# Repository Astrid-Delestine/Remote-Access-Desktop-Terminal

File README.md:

R-DAT 

# NOW IN BETA!

### Notes:

* This project has graduated from a coursework project to a personal project of mine (Astrid)
* Any text with a line thru it will be removed in the next revision (if I remember)
* A **MAJOR** rebuild was done for this version, and as such I do not belive everyting will work out of the gate. 
* Refer to the dev branch for the most up to date snapshots
* Refer to the Alpha branch for the final alpha version
* Refer to the Beta branch for the current Beta version

~~The R-DAT will use a Latte pana MU 8gb [here](https://www.lattepanda.com/lattepanda-mu) & sold [here](https://www.dfrobot.com/kit-004.html?tracking=LATTEPANDAMU) with their github linked [here](https://github.com/LattePandaTeam/LattePanda-Mu).
It can operate at anywhere from 9-20v.~~

~~All project requirements are listed in [here](./Legacy/CourseDocs/proj_req.md)~~

~~For the midterm review please look [here](./Legacy/CourseDocs/MidtermReview.md)~~

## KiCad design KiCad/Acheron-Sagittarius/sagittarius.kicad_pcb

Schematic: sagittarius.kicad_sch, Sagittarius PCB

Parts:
C1: 4.7u; C_0603_1608Metric
C2, C3, C4, C7: 100n; C_0603_1608Metric
C5: 10u; C_0603_1608Metric
C6: 10n; C_0603_1608Metric
C8, C9: 1u; C_0805_2012Metric_Pad1.15x1.40mm_HandSolder
C10, C11: 10n; C_0805_2012Metric_Pad1.15x1.40mm_HandSolder
C12, C13, C14, C15, C16, C17, C18, C19, C20, C21: 100n; C_0805_2012Metric_Pad1.15x1.40mm_HandSolder
CB1: 100n; C_0805_2012Metric_Pad1.15x1.40mm_HandSolder
D1, D2, D3, D4, D5, D6, D7, D8, D9, D10, D11, D12, D13, D14, D15, D16, D17, D18, D19, D20, D21, D22, D23, D24, D25, D26, D27, D28, D29, D30, D31, D32, D33, D34, D35, D36, D37, D38, D39, D40, D41, D42, D43, D44, D45, D46, D47, D48, D49, D50, D51, D52, D53, D54, D55, D56, D57, D58, D59, D60, D61, D62, D63, D64, D65, D66, D67, D68, D69, D70, D71, D72, D74, D75, D76, D77: 1N4148; D_SOD-123
D73: RB060M-60TR; D_SOD-123; Manufacturer Part No RB060M-60TR; LCSC Part No C114257
D78, D79, D80, D81, D82, D83, D84, D85: WS2812-2020; LED_WS2812_2020; Manufacturer Part No WS2812-2020
FB1: 150R@100MHz; L_1812_4532Metric_Pad1.30x3.40mm_HandSolder; Manufacturer Part No FCM3216KF-151T09; LCSC Part No C155090
G1: Lambda; lambda
G2: Cannon Keys Logo; cannon_logo_11.5x7.9mm
G3: Gamma2; gamma2
G4: Acheron Logo; acheronShort_0.3x0.5in_Plated
G5: Delta; delta
G6: Sagittarius Logo; sagittariusLogo_21.4x15.6
G7: Epsilon; epsilon
G8: Sigma; sigma
G9: Sagittarius Name; sagittariusName
G10: Tau; tau
G11: Sagittarius Poem; sagittariusPoem
G12: Phi; phi
G13: Sagittarius Label; sagittariusLabel_30x11.7mm
G14: Zeta; zeta
GR1: Right Space Warning Sign; warning_sign_3.6x3.2mm
GR2: ISO Backslash Warning Sign; warning_sign_3.6x3.2mm
GR3: Split Left Shift Warning Sign; warning_sign_3.6x3.2mm
GR4: Backspace Warning Sign; warning_sign_3.6x3.2mm
J1: Conn_ARM_JTAG_SWD_10
J2: SM04B-SRSS; JST_SM04B-SRSS; Manufacturer Part No SM04B-SRSS-TB(LF)(SN); LCSC Part No C160404
LED1, LED2, LED3, LED4, LED5, LED6, LED7, LED8, LED9, LED10, LED11, LED12, LED13, LED14, LED15, LED16, LED17, LED18, LED19, LED20, LED21, LED22, LED23, LED24, LED25, LED26, LED27, LED28, LED29, LED30, LED31, LED32, LED33, LED34, LED35, LED36, LED37, LED38, LED39, LED40, LED41, LED42, LED43, LED44, LED45, LED46, LED47, LED48, LED49, LED50, LED51, LED52, LED53, LED54, LED55, LED56, LED57, LED58, LED59, LED60, LED61, LED62, LED63, LED64, LED65, LED66, LED67, LED68, LED69, LED70, LED71, LED72, LED73, LED74, LED75, LED76, LED77, LED78, LED79, LED80, LED81, LED82, LED83, LED84: LED; LED_THT_2.54mm
Q1: AO3401A; SOT-23; Manufacturer Part No AO3401; LCSC Part No C427383
Q2: DTC123JKAT146; SOT-23; Manufacturer Part No DTC123JKAT146; LCSC Part No C111724
R1, R5, R6, R7, R8, R17, R18: 10k; R_0805_2012Metric_Pad1.15x1.40mm_HandSolder
R2, R3: 100k; R_0805_2012Metric_Pad1.15x1.40mm_HandSolder
R4, R19: 100R; R_0805_2012Metric_Pad1.15x1.40mm_HandSolder
R9, R10, R11, R12, R13, R14, R15, R16: 3R; R_0805_2012Metric_Pad1.15x1.40mm_HandSolder
RL1, RL2, RL3, RL4, RL5, RL6, RL7, RL8, RL9, RL10, RL11, RL12, RL13, RL14, RL15, RL16, RL17, RL18, RL19, RL20, RL21, RL22, RL23, RL24, RL25, RL26, RL27, RL28, RL29, RL30, RL31, RL32, RL33, RL34, RL35, RL36, RL37, RL38, RL39, RL40, RL41, RL42, RL43, RL44, RL45, RL46, RL47, RL48, RL49, RL50, RL51, RL52, RL53, RL54, RL55, RL56, RL57, RL58, RL59, RL60, RL61, RL62, RL63, RL64, RL65, RL66, RL67, RL68, RL69, RL70, RL71, RL72, RL73, RL74, RL75, RL76, RL77: 420; R_0805_2012Metric_Pad1.15x1.40mm_HandSolder
ROT1, ROT2, ROT3, ROT4: EC11Ex; ALPS_EC11E
S1: PCM12SMTR; SW_SPDT_PCM12; Manufacturer Part No PCM12SMTR; LCSC Part No C221841
S2: SKQGADE010; K2-1187SQ-A4SW-06; Manufacturer Part No SKQGADE010; LCSC Part No C116647
SW1: PGUP; MX100
SW2: ESC; MX100
SW3: 1; MX100
SW4: 2; MX100
SW5: 3; MX100
SW6: 4; MX100
SW7: 5; MX100
SW8: 6; MX100
SW9: 7; MX100
SW10: 8; MX100
SW11: 9; MX100
SW12: 10; MX100
SW13: MINUS; MX100
SW14: PLUS; MX100
SW15: LEFT_BACKSPACE; MX100
SW16: RIGHT BACKSPACE; MX100
SW17: 2U BACKSPACE; MX200
SW18: PGDN; MX100
SW19: TAB; MX150
SW20: Q; MX100
SW21: W; MX100
SW22: E; MX100
SW23: R; MX100
SW24: T; MX100
SW25: Y; MX100
SW26: U; MX100
SW27: I; MX100
SW28: O; MX100
SW29: P; MX100
SW30: LBRACE; MX100
SW31: RBRACE; MX100
SW32: BKSLSH; MX150
SW33: HOME; MX100
SW34: CAPS LOCK; MX175
SW35: A; MX100
SW36: S; MX100
SW37: D; MX100
SW38: F; MX100
SW39: G; MX100
SW40: H; MX100
SW41: J; MX100
SW42: K; MX100
SW43: L; MX100
SW44: COLON; MX100
SW45: QUOTE; MX100
SW46: ISO_TILDE; MX100
SW47: ANSI_ENTER; MX225
SW48: ISO_ENTER; MX_ISOEnter_Vertical_LED
SW49: STEPPED CAPS; MX125
SW50: END; MX100
SW51: 225_LSHIFT; MX225
SW52: ISO_BLACKSLASH; MX100
SW53: Z; MX100
SW54: X; MX100
SW55: C; MX100
SW56: V; MX100
SW57: B; MX100
SW58: N; MX100
SW59: M; MX100
SW60: COMMA; MX100
SW61: DOT; MX100
SW62: SLASH; MX100
SW63: 225_RSHIFT; MX225
SW64: UP; MX100
SW65: SPLIT_RSHIFT_FN; MX100
SW66: 125_LSHIFT; MX125
SW67: 125_RSHIFT; MX125
SW68: LCTRL; MX150
SW69: LGUI; MX125
SW70: 1U_LSPACE; MX100
SW71: 225_LSPACE; MX225
SW72: 275_RSPACE; MX275
SW73: 100_RSPACE; MX100
SW74: DOWN; MX100
SW75: RIGHT; MX100
SW76: 175_LSPACE; MX175
SW77: 150_LSPACE; MX150
SW78: 150_RALT; MX150
SW79: 150_RCTRL; MX150
SW80: 175_RSPACE; MX175
SW81: LEFT; MX100
U1: STM32F072-LQFP48; LQFP-48_7x7mm_P0.5mm; Manufacturer Part No STM32F072CBT6; LCSC Part No C81720
U2: MCP1700-3302E_SOT23; SOT-23; Manufacturer Part No MCP1700-3302E/TT; LCSC Part No C39051
U3: TXS0101; SOT-23-6; Manufacturer Part Number TXS0101DBVR; LCSC Part Number C132604

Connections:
3V3: C1.2, C2.2, C3.2, C4.2, C5.1, C6.1, C7.2, C9.2, C12.2, D73.2 (A), J1.1 (VTref), R3.1, R5.2, R6.2, R17.1, S1.3 (C), U1.1 (VBAT), U1.9 (VDDA), U1.24 (VDD), U1.36 (VDDIO2), U1.48 (VDD), U2.2 (VO), U3.1 (VCCA), U3.5 (OE)
5V: C8.2, C13.1, D73.1 (K), J2.1, Q1.2 (S), R2.1, R9.1, R10.1, R11.1, R12.1, R13.1, R14.1, R15.1, R16.1, R18.2, U2.3 (VI), U3.6 (VCCB)
BOOT0: R1.2, U1.44 (BOOT0)
Col1: ROT1.S1, ROT2.S1, ROT3.S1, ROT4.S1, SW1.1 (Col), SW18.1 (Col), SW33.1 (Col), SW50.1 (Col), SW68.1 (Col), U1.17 (PA7/TIM3_CH2/TIM14_CH1/ADC_IN7)
Col2: SW2.1 (Col), SW19.1 (Col), SW34.1 (Col), SW49.2 (Row), SW51.1 (Col), SW66.1 (Col), SW69.1 (Col), U1.15 (PA5/ADC_IN5/DAC_OUT2)
Col3: SW3.1 (Col), SW20.1 (Col), SW35.1 (Col), SW52.1 (Col), U1.14 (PA4/TIM14_CH1/ADC_IN4)
Col4: SW4.1 (Col), SW21.1 (Col), SW36.1 (Col), SW53.1 (Col), U1.13 (PA3/TIM15_CH2/ADC_IN3)
Col5: SW5.1 (Col), SW22.1 (Col), SW37.1 (Col), SW54.1 (Col), U1.12 (PA2/ADC_IN2)
Col6: SW6.1 (Col), SW23.1 (Col), SW38.1 (Col), SW55.1 (Col), U1.11 (PA1/ADC_IN1)
Col7: SW7.1 (Col), SW24.1 (Col), SW39.1 (Col), SW56.1 (Col), SW70.1 (Col), SW76.2 (Row), U1.10 (PA0/ADC_IN0)
Col8: SW8.1 (Col), SW25.1 (Col), SW40.1 (Col), SW57.1 (Col), SW71.1 (Col), SW77.2 (Row), U1.41 (SPI1_MOSI/I2S1_SD/TIM3_CH2/PB5)
Col9_SWDIO: J1.2 (SWDIO/TMS), SW9.1 (Col), SW26.1 (Col), SW41.1 (Col), SW58.1 (Col), SW72.1 (Col), SW80.1 (Col), U1.34 (SWDIO/PA13)
Col10: SW10.1 (Col), SW27.1 (Col), SW42.1 (Col), SW59.1 (Col), SW73.1 (Col), U1.20 (PB2)
Col11: SW11.1 (Col), SW28.1 (Col), SW43.1 (Col), SW60.1 (Col), U1.19 (PB1/TIM3_CH4/TIM14_CH1/ADC_IN9)
Col12: SW12.1 (Col), SW29.1 (Col), SW44.1 (Col), SW61.1 (Col), U1.18 (PB0/TIM3_CH3/ADC_IN8)
Col13: SW13.1 (Col), SW30.1 (Col), SW45.1 (Col), SW62.1 (Col), U1.46 (SPI2_NSS/I2S2_WS/I2C1_SDA/TIM17_CH1/PB9)
Col14: SW14.1 (Col), SW31.1 (Col), SW46.1 (Col), SW63.1 (Col), SW67.1 (Col), SW78.1 (Col), SW81.2 (Row), U1.45 (I2C1_SCL/TIM16_CH1/PB8)
Col15: SW15.1 (Col), SW17.1 (Col), SW32.1 (Col), SW47.1 (Col), SW64.1 (Col), SW74.1 (Col), U1.43 (2C1_SDA/PB7)
Col16: SW16.1 (Col), SW48.1 (Col), SW65.1 (Col), SW75.1 (Col), SW79.2 (Row), U1.42 (I2C1_SCL/PB6)
D+: J2.3, U1.33 (USB_DP/PA12)
D-: J2.2, U1.32 (USB_DM/TIM1_CH4/PA11)
EncA: R6.1, R8.2, ROT1.A, ROT2.A, ROT3.A, ROT4.A
EncB: R5.1, R7.2, ROT1.B, ROT2.B, ROT3.B, ROT4.B
EncOutA: C11.2, R8.1, U1.22 (PB11/TIM2_CH4/I2C2_SDA)
EncOutB: C10.2, R7.1, U1.25 (PB12)
GND: C1.1, C2.1, C3.1, C4.1, C5.2, C6.2, C7.1, C8.1, C9.1, C10.1, C11.1, C12.1, C13.2, C14.2, C15.2, C16.2, C17.2, C18.2, C19.2, C20.2, C21.2, CB1.2, D78.2 (VSS), D79.2 (VSS), D80.2 (VSS), D81.2 (VSS), D82.2 (VSS), D83.2 (VSS), D84.2 (VSS), D85.2 (VSS), FB1.1, J1.3 (GND), J1.5 (GND), J1.9 (GNDDetect), J2.4, LED1.K, LED2.K, LED3.K, LED4.K, LED5.K, LED6.K, LED7.K, LED8.K, LED9.K, LED10.K, LED11.K, LED12.K, LED13.K, LED14.K, LED15.K, LED16.K, LED17.K, LED18.K, LED19.K, LED20.K, LED21.K, LED22.K, LED23.K, LED24.K, LED25.K, LED26.K, LED27.K, LED28.K, LED29.K, LED30.K, LED31.K, LED32.K, LED33.K, LED34.K, LED35.K, LED36.K, LED37.K, LED38.K, LED39.K, LED40.K, LED41.K, LED42.K, LED43.K, LED44.K, LED45.K, LED46.K, LED47.K, LED48.K, LED49.K, LED50.K, LED51.K, LED52.K, LED53.K, LED54.K, LED55.K, LED56.K, LED57.K, LED58.K, LED59.K, LED60.K, LED61.K, LED62.K, LED63.K, LED64.K, LED65.K, LED66.K, LED67.K, LED68.K, LED69.K, LED70.K, LED71.K, LED72.K, LED73.K, LED74.K, LED75.K, LED76.K, LED77.K, LED78.K, LED79.K, LED80.K, LED81.K, LED82.K, LED83.K, LED84.K, Q2.2 (E), R2.2, R3.2, R17.2, S1.1 (A), S2.1, U1.8 (VSSA), U1.23 (VSS), U1.35 (VSS), U1.47 (VSS), U2.1 (GND), U3.2 (GND)
GNDPWR: FB1.2, ROT1.S (Shield), ROT2.S (Shield), ROT3.S (Shield), ROT4.S (Shield)
INDICATOR1: RL1.1, U1.40 (SPI1_MISO/I2S1_MCK/TIM3_CH1/PB4)
INDICATOR2: RL2.1, U1.39 (SPI1_SCK/I2S1_CK/TIM2_CH2/PB3)
INDICATOR3: RL3.1, U1.38 (PA2)
LED_PWM: Q2.1 (B), U1.16 (PA6/ADC_IN6/TIM3_CH1/TIM16_CH1)
NRST: CB1.1, J1.10 (~RESET~), R4.2, U1.7 (NRST)
unnamed: C14.1, D78.4 (VDD), R9.2
unnamed: C15.1, D79.4 (VDD), R10.2
unnamed: C16.1, D80.4 (VDD), R11.2
unnamed: C17.1, D81.4 (VDD), R12.2
unnamed: C18.1, D82.4 (VDD), R13.2
unnamed: C19.1, D83.4 (VDD), R14.2
unnamed: C20.1, D84.4 (VDD), R15.2
unnamed: C21.1, D85.4 (VDD), R16.2
unnamed: D2.2 (A), SW2.2 (Row)
unnamed: D3.2 (A), SW3.2 (Row)
unnamed: D4.2 (A), SW4.2 (Row)
unnamed: D5.2 (A), SW5.2 (Row)
unnamed: D6.2 (A), SW6.2 (Row)
unnamed: D7.2 (A), SW7.2 (Row)
unnamed: D8.2 (A), SW8.2 (Row)
unnamed: D9.2 (A), SW9.2 (Row)
unnamed: D10.2 (A), SW10.2 (Row)
unnamed: D11.2 (A), SW11.2 (Row)
unnamed: D12.2 (A), SW12.2 (Row)
unnamed: D13.2 (A), SW13.2 (Row)
unnamed: D14.2 (A), SW14.2 (Row)
unnamed: D15.2 (A), SW15.2 (Row), SW17.2 (Row)
unnamed: D16.2 (A), SW16.2 (Row)
unnamed: D18.2 (A), SW19.2 (Row)
unnamed: D19.2 (A), SW20.2 (Row)
unnamed: D20.2 (A), SW21.2 (Row)
unnamed: D21.2 (A), SW22.2 (Row)
unnamed: D22.2 (A), SW23.2 (Row)
unnamed: D23.2 (A), SW24.2 (Row)
unnamed: D24.2 (A), SW25.2 (Row)
unnamed: D25.2 (A), SW26.2 (Row)
unnamed: D26.2 (A), SW27.2 (Row)
unnamed: D27.2 (A), SW28.2 (Row)
unnamed: D28.2 (A), SW29.2 (Row)
unnamed: D29.2 (A), SW30.2 (Row)
unnamed: D30.2 (A), SW31.2 (Row)
unnamed: D31.2 (A), SW32.2 (Row)
unnamed: D33.2 (A), SW34.2 (Row), SW49.1 (Col)
unnamed: D34.2 (A), SW35.2 (Row)
unnamed: D35.2 (A), SW36.2 (Row)
unnamed: D36.2 (A), SW37.2 (Row)
unnamed: D37.2 (A), SW38.2 (Row)
unnamed: D38.2 (A), SW39.2 (Row)
unnamed: D39.2 (A), SW40.2 (Row)
unnamed: D40.2 (A), SW41.2 (Row)
unnamed: D41.2 (A), SW42.2 (Row)
unnamed: D42.2 (A), SW43.2 (Row)
unnamed: D43.2 (A), SW44.2 (Row)
unnamed: D44.2 (A), SW45.2 (Row)
unnamed: D45.2 (A), SW46.2 (Row)
unnamed: D46.2 (A), SW47.2 (Row)
unnamed: D47.2 (A), SW48.2 (Row)
unnamed: D50.2 (A), SW52.2 (Row)
unnamed: D51.2 (A), SW53.2 (Row)
unnamed: D52.2 (A), SW54.2 (Row)
unnamed: D53.2 (A), SW55.2 (Row)
unnamed: D54.2 (A), SW56.2 (Row)
unnamed: D55.2 (A), SW57.2 (Row)
unnamed: D56.2 (A), SW58.2 (Row)
unnamed: D57.2 (A), SW59.2 (Row)
unnamed: D58.2 (A), SW60.2 (Row)
unnamed: D59.2 (A), SW61.2 (Row)
unnamed: D60.2 (A), SW62.2 (Row)
unnamed: D61.2 (A), SW63.2 (Row), SW67.2 (Row)
unnamed: D63.2 (A), SW65.2 (Row)
unnamed: D64.2 (A), SW68.2 (Row)
unnamed: D66.2 (A), SW70.2 (Row), SW76.1 (Col)
unnamed: D67.2 (A), SW71.2 (Row), SW77.1 (Col)
unnamed: D49.2 (A), SW51.2 (Row), SW66.2 (Row)
unnamed: D68.2 (A), SW72.2 (Row), SW80.2 (Row)
unnamed: D74.2 (A), ROT1.C
unnamed: D69.2 (A), SW73.2 (Row)
unnamed: D70.2 (A), SW78.2 (Row), SW81.1 (Col)
unnamed: D71.2 (A), SW74.2 (Row)
unnamed: D72.2 (A), SW75.2 (Row), SW79.1 (Col)
unnamed: D78.1 (DOUT), D79.3 (DIN)
unnamed: D79.1 (DOUT), D80.3 (DIN)
unnamed: D80.1 (DOUT), D81.3 (DIN)
unnamed: D81.1 (DOUT), D82.3 (DIN)
unnamed: D82.1 (DOUT), D83.3 (DIN)
unnamed: D83.1 (DOUT), D84.3 (DIN)
unnamed: D84.1 (DOUT), D85.3 (DIN)
unnamed: D62.2 (A), SW64.2 (Row)
unnamed: D65.2 (A), SW69.2 (Row)
unnamed: D75.2 (A), ROT2.C
unnamed: D76.2 (A), ROT3.C
unnamed: D77.2 (A), ROT4.C
unnamed: LED4.A, RL4.1
unnamed: LED5.A, RL5.2
unnamed: LED6.A, RL6.2
unnamed: LED7.A, RL7.2
unnamed: LED8.A, RL8.2
unnamed: LED9.A, RL9.2
unnamed: LED10.A, RL10.2
unnamed: LED11.A, RL11.2
unnamed: LED12.A, RL12.2
unnamed: LED13.A, RL13.2
unnamed: LED14.A, RL14.2
unnamed: LED15.A, RL15.2
unnamed: LED16.A, RL16.2
unnamed: LED17.A, RL17.2
unnamed: LED18.A, LED19.A, RL18.2
unnamed: LED20.A, RL19.2
unnamed: LED21.A, RL20.2
unnamed: LED22.A, RL21.2
unnamed: LED23.A, RL22.2
unnamed: LED24.A, RL23.2
unnamed: LED25.A, RL24.2
unnamed: LED26.A, RL25.2
unnamed: LED27.A, RL26.2
unnamed: LED28.A, RL27.2
unnamed: LED29.A, RL28.2
unnamed: LED30.A, RL29.2
unnamed: LED31.A, RL30.2
unnamed: LED32.A, RL31.2
unnamed: LED33.A, RL32.2
unnamed: LED34.A, RL33.2
unnamed: LED35.A, RL34.2
unnamed: LED36.A, RL35.2
unnamed: LED51.A, LED52.A, RL50.2
unnamed: LED37.A, RL36.2
unnamed: LED38.A, RL37.2
unnamed: LED39.A, RL38.2
unnamed: LED40.A, RL39.2
unnamed: LED41.A, RL40.2
unnamed: LED42.A, RL41.2
unnamed: LED43.A, RL42.2
unnamed: LED44.A, RL43.2
unnamed: LED45.A, RL44.2
unnamed: LED46.A, RL45.2
unnamed: LED47.A, RL46.2
unnamed: LED48.A, RL47.2
unnamed: LED49.A, RL48.2
unnamed: LED50.A, RL49.2
unnamed: LED53.A, RL51.2
unnamed: LED54.A, RL52.2
unnamed: LED55.A, RL53.2
unnamed: LED56.A, RL54.2
unnamed: LED57.A, RL55.2
unnamed: LED58.A, RL56.2
unnamed: LED59.A, RL57.2
unnamed: LED60.A, RL58.2
unnamed: LED61.A, RL59.2
unnamed: LED62.A, RL60.2
unnamed: LED63.A, RL61.2
unnamed: LED64.A, RL62.2
unnamed: LED65.A, RL63.2
unnamed: LED66.A, RL64.2
unnamed: LED67.A, RL65.2
unnamed: LED68.A, RL66.2
unnamed: LED69.A, RL67.2
unnamed: LED70.A, RL68.2
unnamed: LED81.A, RL75.2
unnamed: LED82.A, RL76.2
unnamed: LED83.A, LED84.A, RL77.2
unnamed: LED71.A, LED72.A, RL69.2
unnamed: LED73.A, LED74.A, RL70.2
unnamed: LED75.A, RL71.2
unnamed: LED76.A, RL72.2
unnamed: LED77.A, LED78.A, RL73.2
unnamed: LED79.A, LED80.A, RL74.2
unnamed: LED1.A, RL1.2
unnamed: LED2.A, RL2.2
unnamed: LED3.A, RL3.2
unnamed: Q1.1 (G), R19.1
unnamed: Q1.3 (D), RL4.2, RL5.1, RL6.1, RL7.1, RL8.1, RL9.1, RL10.1, RL11.1, RL12.1, RL13.1, RL14.1, RL15.1, RL16.1, RL17.1, RL18.1, RL19.1, RL20.1, RL21.1, RL22.1, RL23.1, RL24.1, RL25.1, RL26.1, RL27.1, RL28.1, RL29.1, RL30.1, RL31.1, RL32.1, RL33.1, RL34.1, RL35.1, RL36.1, RL37.1, RL38.1, RL39.1, RL40.1, RL41.1, RL42.1, RL43.1, RL44.1, RL45.1, RL46.1, RL47.1, RL48.1, RL49.1, RL50.1, RL51.1, RL52.1, RL53.1, RL54.1, RL55.1, RL56.1, RL57.1, RL58.1, RL59.1, RL60.1, RL61.1, RL62.1, RL63.1, RL64.1, RL65.1, RL66.1, RL67.1, RL68.1, RL69.1, RL70.1, RL71.1, RL72.1, RL73.1, RL74.1, RL75.1, RL76.1, RL77.1
unnamed: Q2.3 (C), R18.1, R19.2
unnamed: R1.1, S1.2 (B)
unnamed: R4.1, S2.2
RGB_3V3: U1.28 (SPI2_MOSI/I2S2_SD/PB15), U3.3 (A)
RGB_5V: D78.3 (DIN), U3.4 (B)
ROT1S2: D1.2 (A), ROT1.S2, SW1.2 (Row)
ROT2S2: D17.2 (A), ROT2.S2, SW18.2 (Row)
ROT3S2: D32.2 (A), ROT3.S2, SW33.2 (Row)
ROT4S2: D48.2 (A), ROT4.S2, SW50.2 (Row)
Row1: D1.1 (K), D2.1 (K), D3.1 (K), D4.1 (K), D5.1 (K), D6.1 (K), D7.1 (K), D8.1 (K), D74.1 (K), U1.21 (PB10/SPI2_SCK/I2C2_SCL/TIM2_CH3)
Row2: D17.1 (K), D18.1 (K), D19.1 (K), D20.1 (K), D21.1 (K), D22.1 (K), D23.1 (K), D75.1 (K), U1.27 (PB14/SPI2_MISO/I2S2_MCK/I2C2_SDA/TIM15_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)
Row3: D32.1 (K), D33.1 (K), D34.1 (K), D35.1 (K), D36.1 (K), D37.1 (K), D38.1 (K), D76.1 (K), U1.29 (TIM1_CH1/PA8)
Row4: D48.1 (K), D49.1 (K), D50.1 (K), D51.1 (K), D52.1 (K), D53.1 (K), D54.1 (K), D55.1 (K), D77.1 (K), U1.30 (TIM1_CH2/PA9)
Row5: D64.1 (K), D65.1 (K), D66.1 (K), D67.1 (K), U1.31 (TIM1_CH3/PA10)
Row6: D9.1 (K), D10.1 (K), D11.1 (K), D12.1 (K), D13.1 (K), D14.1 (K), D15.1 (K), D16.1 (K), U1.2 (PC13)
Row7: D24.1 (K), D25.1 (K), D26.1 (K), D27.1 (K), D28.1 (K), D29.1 (K), D30.1 (K), D31.1 (K), U1.3 (PC14/OSC32_IN)
Row8: D39.1 (K), D40.1 (K), D41.1 (K), D42.1 (K), D43.1 (K), D44.1 (K), D45.1 (K), D46.1 (K), D47.1 (K), U1.4 (PC15/OSC32_OUT)
Row9: D56.1 (K), D57.1 (K), D58.1 (K), D59.1 (K), D60.1 (K), D61.1 (K), D62.1 (K), D63.1 (K), U1.5 (PF0/OSC_IN)
Row10: D68.1 (K), D69.1 (K), D70.1 (K), D71.1 (K), D72.1 (K), U1.6 (PF1/OSC_OUT)
SWCLK: J1.4 (SWDCLK/TCK), U1.37 (SWCLK/PA14)

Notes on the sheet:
Switch LED matrix
SWD
Indicators
Daughterboard connector
Switch matrix
MCU
RGB
Graphics
Encoders
Power supply and protection circuit
CSI for Capacitor - Source Input CSO for Capacitor - Souce Output
Hard reset circuit

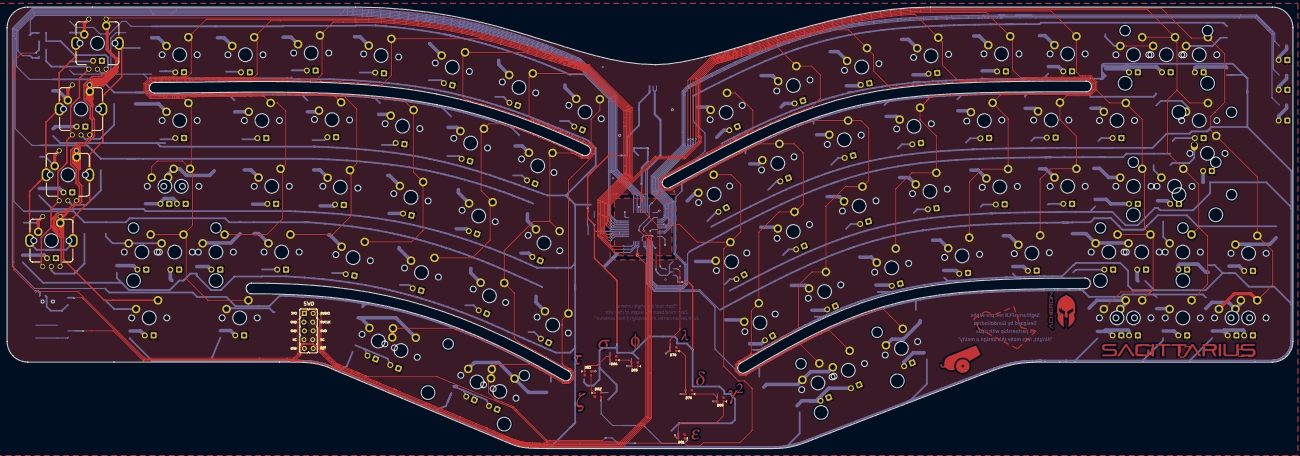
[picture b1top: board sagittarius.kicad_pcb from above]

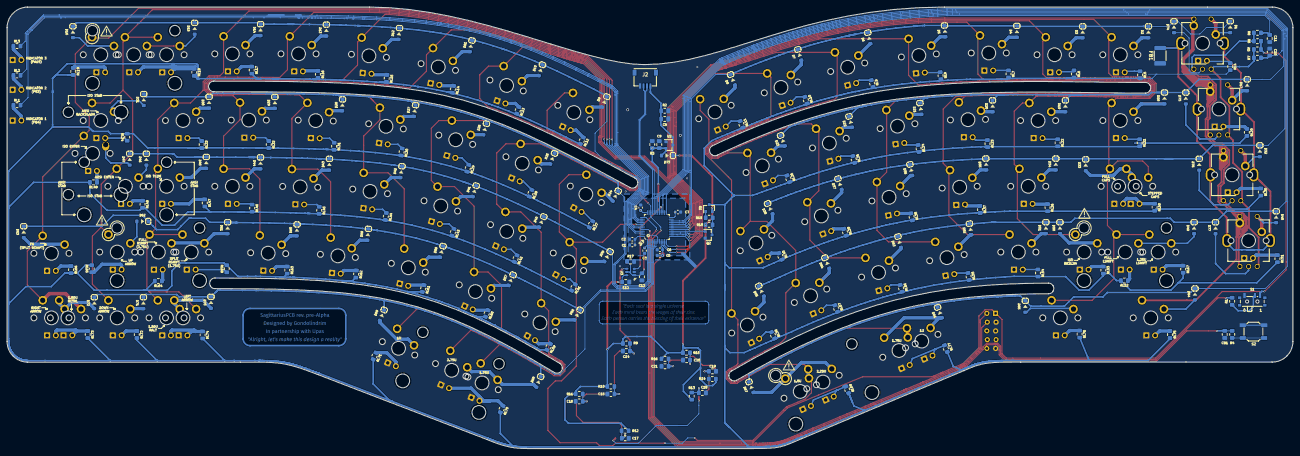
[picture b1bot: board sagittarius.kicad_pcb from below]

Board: 2 copper layers, 372.4 x 127.9 mm, 400 parts (379 on the bottom side), 218 nets.
